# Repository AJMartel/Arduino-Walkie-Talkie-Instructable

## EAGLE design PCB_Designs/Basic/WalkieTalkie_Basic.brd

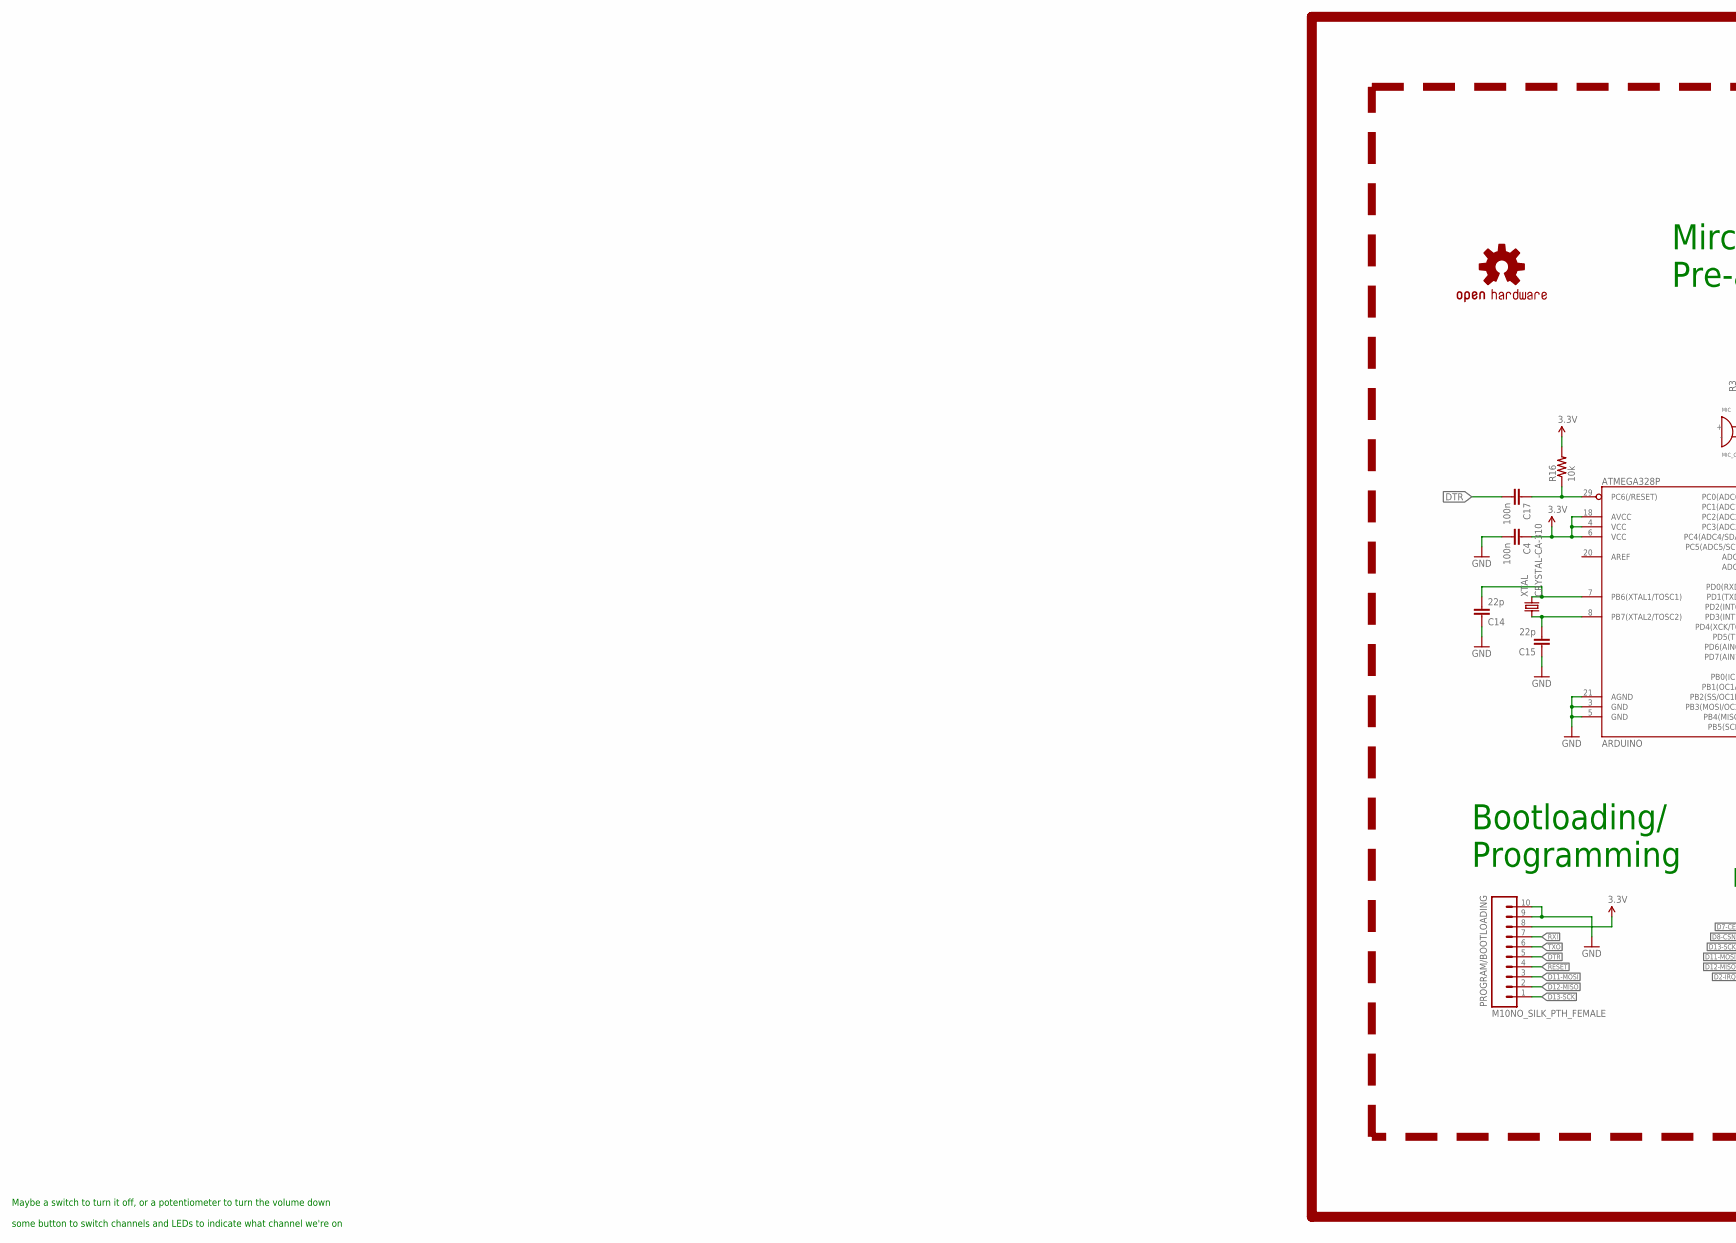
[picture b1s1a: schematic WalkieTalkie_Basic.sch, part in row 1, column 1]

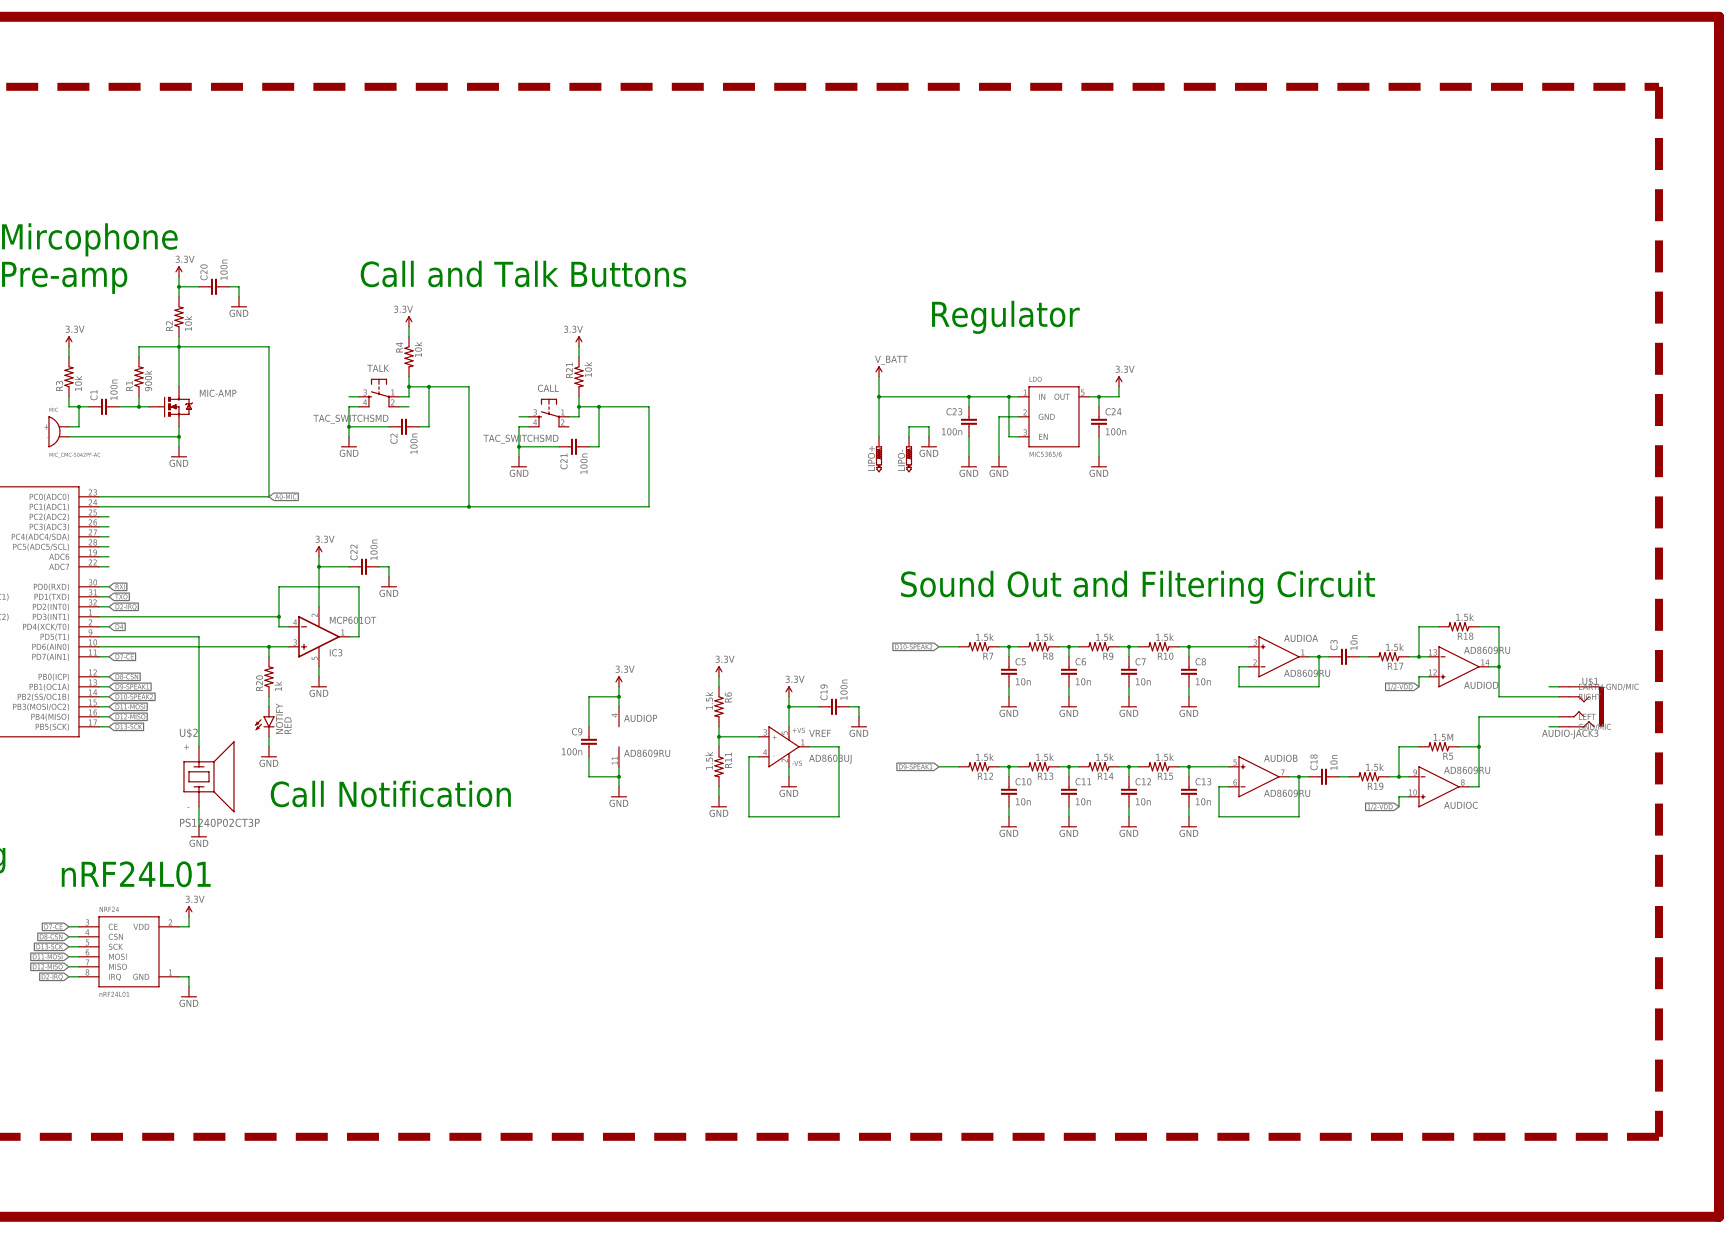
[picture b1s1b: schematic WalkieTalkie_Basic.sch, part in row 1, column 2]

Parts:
ARDUINO: ATMEGA328P; TQFP32-08
AUDIO: AD8609RU; TSSOP14
C1, C2, C4, C9, C17, C19, C20, C21, C22, C23, C24: 100n; C0402
C3, C5, C6, C7, C8, C10, C11, C12, C13, C18: 10n; C0402
C14, C15: 22p; C0402
CALL: TAC_SWITCHSMD; TACTILE-SWITCH-SMD
IC3: MCP601OT; SOT23-5
LDO: MIC5365/6; SC-70-5
LIPO: BATT-CONNECT; HOLE
LOGO1: OSHW-LOGOS; OSHW-LOGO-S
MIC: MIC_CMC-5042PF-AC; MIC_01
MIC-AMP: MOSFET-NCHANNELBSS123LT1G; SOT23-3
NOTIFY: RED; LED-0603
NRF24: NRF24L01-BREAKOUT
PROGRAM/BOOTLOADING: M10NO_SILK_PTH_FEMALE; 1X10_NO_SILK
R1: 900k; R0402
R2, R3, R4, R16, R21: 10k; R0402
R5: 1.5M; R0402
R6, R7, R8, R9, R10, R11, R12, R13, R14, R15, R17, R18, R19: 1.5k; R0402
R20: 1k; R0402
TALK: TAC_SWITCHSMD; TACTILE-SWITCH-SMD
U$1: AUDIO-JACK3; AUDIO-JACK-TRRS-SMD
U$2: PS1240P02CT3P; PIEZO-1
VREF: AD8603UJ; SOT23-5
XTAL: CRYSTAL-CA-310; CA-301

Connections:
1/2-VDD: AUDIO.10 (IN+), AUDIO.12 (IN+), VREF.1 (OUT), VREF.4 (IN-)
3.3V: ARDUINO.4 (VCC), ARDUINO.6 (VCC), ARDUINO.18 (AVCC), AUDIO.4 (V+), C4.1, C9.1, C19.1, C20.1, C22.1, C24.1, IC3.2 (V-), LDO.5 (OUT), NRF24.2 (VDD), PROGRAM/BOOTLOADING.8, R2.2, R3.2, R4.1, R6.1, R16.2, R21.1, VREF.5 (+VS)
A0-MIC: ARDUINO.23 (PC0(ADC0)), MIC-AMP.3 (D), R1.2, R2.1
D2-IRQ: ARDUINO.32 (PD2(INT0)), NRF24.8 (IRQ)
D3: ARDUINO.1 (PD3(INT1)), IC3.1 (OUT), IC3.4 (-IN)
D4: ARDUINO.2 (PD4(XCK/T0))
D5: ARDUINO.9 (PD5(T1)), U$2.+
D6: ARDUINO.10 (PD6(AIN0)), IC3.3 (+IN), R20.2
D7-CE: ARDUINO.11 (PD7(AIN1)), NRF24.3 (CE)
D8-CSN: ARDUINO.12 (PB0(ICP)), NRF24.4 (CSN)
D9-SPEAK1: ARDUINO.13 (PB1(OC1A)), R12.2
D10-SPEAK2: ARDUINO.14 (PB2(SS/OC1B)), R7.2
D11-MOSI: ARDUINO.15 (PB3(MOSI/OC2)), NRF24.6 (MOSI), PROGRAM/BOOTLOADING.3
D12-MISO: ARDUINO.16 (PB4(MISO)), NRF24.7 (MISO), PROGRAM/BOOTLOADING.2
D13-SCK: ARDUINO.17 (PB5(SCK)), NRF24.5 (SCK), PROGRAM/BOOTLOADING.1
DTR: C17.2, PROGRAM/BOOTLOADING.5
GND: ARDUINO.3 (GND), ARDUINO.5 (GND), ARDUINO.21 (AGND), AUDIO.11 (V-), C2.1, C4.2, C5.2, C6.2, C7.2, C8.2, C9.2, C10.2, C11.2, C12.2, C13.2, C14.1, C15.1, C19.2, C20.2, C21.1, C22.2, C23.2, C24.2, CALL.4, IC3.5 (V+), LDO.2 (GND), LIPO.P$2, MIC.-, MIC-AMP.2 (S), NOTIFY.C, NRF24.1 (GND), PROGRAM/BOOTLOADING.9, PROGRAM/BOOTLOADING.10, R11.2, TALK.4, U$2.-, VREF.2 (-VS)
unnamed: AUDIO.14 (OUT), R18.1, U$1.RING1 (RIGHT)
unnamed: AUDIO.8 (OUT), R5.1, U$1.TIP (LEFT)
unnamed: C1.2, MIC-AMP.1 (G), R1.1
unnamed: NOTIFY.A, R20.1
unnamed: AUDIO.1 (OUT), AUDIO.2 (IN-), C3.1
unnamed: C1.1, MIC.+, R3.1
unnamed: R6.2, R11.1, VREF.3 (IN+)
unnamed: C6.1, R8.1, R9.2
unnamed: C7.1, R9.1, R10.2
unnamed: AUDIO.3 (IN+), C8.1, R10.1
unnamed: C5.1, R7.1, R8.2
unnamed: C11.1, R13.1, R14.2
unnamed: C12.1, R14.1, R15.2
unnamed: AUDIO.5 (IN+), C13.1, R15.1
unnamed: C10.1, R12.1, R13.2
unnamed: ARDUINO.7 (PB6(XTAL1/TOSC1)), C14.2, XTAL.2
unnamed: ARDUINO.8 (PB7(XTAL2/TOSC2)), C15.2, XTAL.1
unnamed: C3.2, R17.2
unnamed: AUDIO.13 (IN-), R17.1, R18.2
unnamed: AUDIO.6 (IN-), AUDIO.7 (OUT), C18.1
unnamed: AUDIO.9 (IN-), R5.2, R19.1
unnamed: C18.2, R19.2
RESET: ARDUINO.29 (PC6(/RESET)), C17.1, PROGRAM/BOOTLOADING.4, R16.1
RXI: ARDUINO.30 (PD0(RXD)), PROGRAM/BOOTLOADING.7
TALK/CALL: ARDUINO.24 (PC1(ADC1)), C2.2, C21.2, CALL.1, R4.2, R21.2, TALK.1
TXO: ARDUINO.31 (PD1(TXD)), PROGRAM/BOOTLOADING.6
V_BATT: C23.1, LDO.1 (IN), LDO.3 (EN), LIPO.P$1

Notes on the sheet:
Maybe a switch to turn it off, or a potentiometer to turn the volume down some button to switch channels and LEDs to indicate what channel we're on
Regulator
Sound Out and Filtering Circuit
Mircophone Pre-amp
Call and Talk Buttons
Call Notification
nRF24L01
Bootloading/ Programming

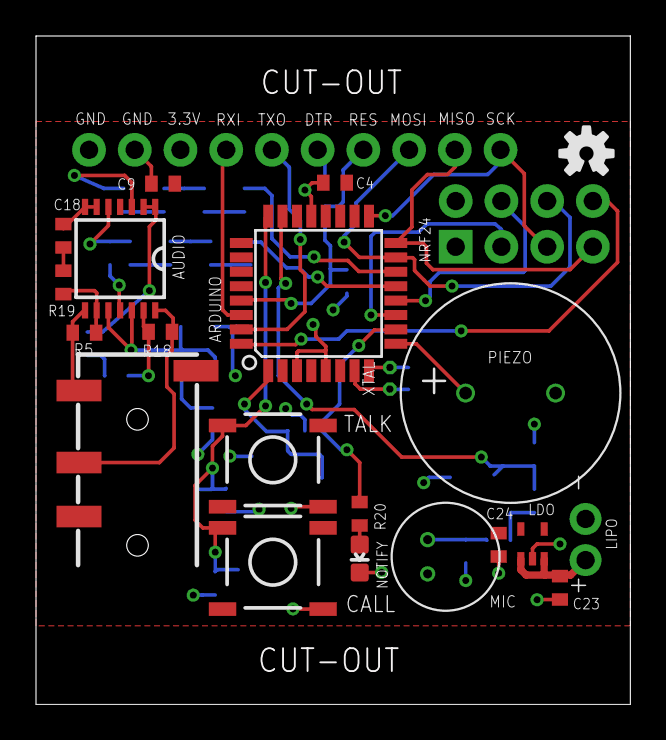
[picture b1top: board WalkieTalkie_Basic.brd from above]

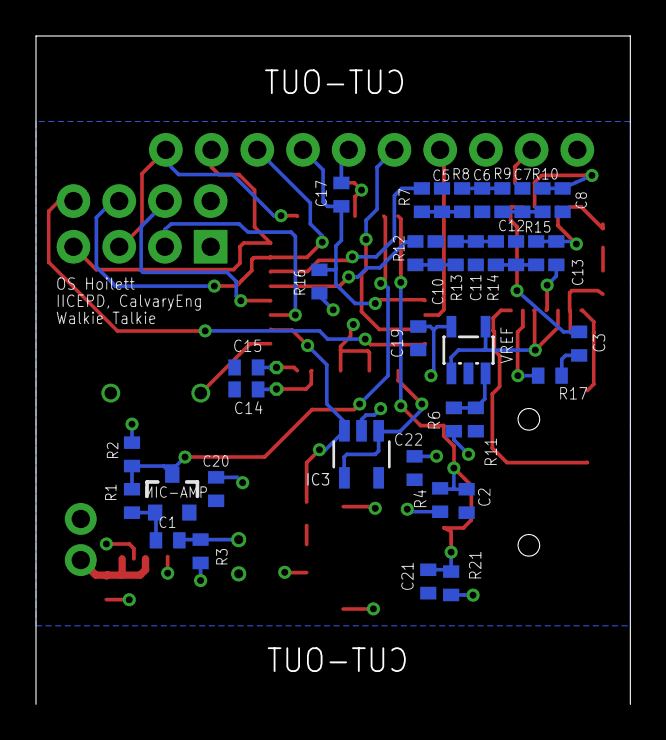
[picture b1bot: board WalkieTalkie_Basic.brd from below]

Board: 2 copper layers, 33.0 x 37.1 mm, 61 parts (38 on the bottom side), 43 nets.

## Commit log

2016-03-09 Added files via upload
2016-05-04 removed .b#x and .s#x autosave Eagle files
2016-05-04 updating code to respond to call button and Mighty Morphin Power Rangers Communicator Sound
2016-05-05 added audio filtering circuit
2016-05-05 testing gitignore again
2016-05-05 updated gitignore
2016-05-05 removed .b#x and .s#x files
2016-05-08 updates to new prototype walkie talkie code to include notification
2016-05-08 updating pcb design with labels, removed extra button, added library part for nRF24L01 breakout, etc
2016-05-10 added a reminder to add volume control to PCB design
2016-05-10 added bill of materials and datasheets
2016-05-12 updated code to include Call button and plays Mighty Morphin Power Rangers Communicator note. Also added a project log
2016-05-12 updating PCB design with buttons, LED indicators, etc.
2016-05-12 updating PCB design and adding more datasheets
2016-05-13 more PCB updates and more datasheets
2016-05-14 more updates
2016-05-15 updates to PCB
2016-05-17 more updates to PCB almost done
2016-05-18 more updates almost done
2016-05-25 updates. almost done
2016-05-26 finished board design. sent to fab (OSH Park)
2016-06-02 modified RF24Audio.cpp file to output HIGH on digital pin 6 when audio is being transmitted and LOW when audio is not being transmitted. This enables the call feature with the Mighty Morphin Power Ra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
2016-06-11 added pictures and videos folder
2016-06-11 updated pcb files with comments, labels, etc
2016-06-11 removed RF24.Libraries.zip file
2016-06-11 updates by adding comments and naming melody to PwrRngrs

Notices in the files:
parts and their libraries:
SparkFun-DiscreteSemi: Licensing: Creative Commons ShareAlike 4.0 International - https://creativecommons.org/licenses/by-sa/4.0
